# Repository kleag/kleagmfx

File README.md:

# Kleag's MFX

ADS1115
MCP23017
https://github.com/adafruit/Adafruit-MCP23017-Arduino-Library#pin-addressing

KY-040
n°4 on MCP@0x20
    - sw pin B1 (9)
    - but on A0, B0 (0, 8)

Pisound
Raspberry Pi 5 (4 should be OK)

Joystick: ADS.P0, ADS.P1
sudo apt install python3-uinput
sudo nano /etc/modules
uinput

Expression Pedal: ADS.P2

sudo nano /etc/udev/rules.d/99-uinput.rules
KERNEL=="uinput", SUBSYSTEM=="misc", MODE="0660", GROUP="input"
sudo usermod -a -G input $USER

`/boot/firmware/config.txt`:
```
display_auto_detect=1
dtparam=i2c_arm=on
dtparam=spi=on
dtparam=i2c_arm_baudrate=400000
dtoverlay=
dtoverlay=pisound
dtoverlay=vc4-kms-v3d
usb_max_current_enable=1
```

sudo raspi-config
```

Then go to:
`Interface Options → I2C → Enable → Reboot the Pi.`

```bash
sudo apt install -y i2c-tools
```

```bash
sudo i2cdetect -y 1
```

`/home/gael/.config/systemd/user/multieffect.service`
`/home/gael/.config/systemd/user/default.target.wants/multieffect.service -> /home/gael/.config/systemd/user/multieffect.service`

```ini
[Unit]
Description=Start Guitar Multi-Effect Python Script
After=graphical-session.target

[Service]
ExecStart=python /home/gael/multieffects/multieffect.py
WorkingDirectory=/home/gael
Restart=on-failure

[Install]
WantedBy=default.target
```

```bash
journalctl --user-unit multieffect.service
systemctl --user disable multieffect.service
systemctl --user enable multieffect.service
systemctl --user stop multieffect.service
systemctl --user start multieffect.service
```

# Disable wlan power management 
To avoid losing Wifi unexpectedly, disable its power management. Create `/etc/systemd/system/wifi-fix.service`:

```ini
[Unit]
Description=Disable WiFi Power Management
After=network.target

[Service]
Type=oneshot
ExecStart=/sbin/iwconfig wlan0 power off
RemainAfterExit=yes

[Install]
WantedBy=multi-user.target
```

and then enable the new service:
```bash
sudo systemctl enable wifi-fix.service
sudo systemctl start wifi-fix.service
```

# License

Copyright Gaël de Chalendar, 2025-2026.
This source describes Open Hardware and is licensed under the CERN-OHL-
W v2.
You may redistribute and modify this documentation and make products
using it under the terms of the CERN-OHL-W v2 (https:/cern.ch/cern-ohl).
This documentation is distributed WITHOUT ANY EXPRESS OR IMPLIED
WARRANTY, INCLUDING OF MERCHANTABILITY, SATISFACTORY QUALITY
AND FITNESS FOR A PARTICULAR PURPOSE. Please see the CERN-OHL-W v2
for applicable conditions.
Source location: https://github.com/kleag/kleagmfx
As per CERN-OHL-W v2 section 4.1, should You produce hardware based on
these sources, You must maintain the Source Location visible on the
external case of the Kleag's MFX or other product you make using
this documentation.

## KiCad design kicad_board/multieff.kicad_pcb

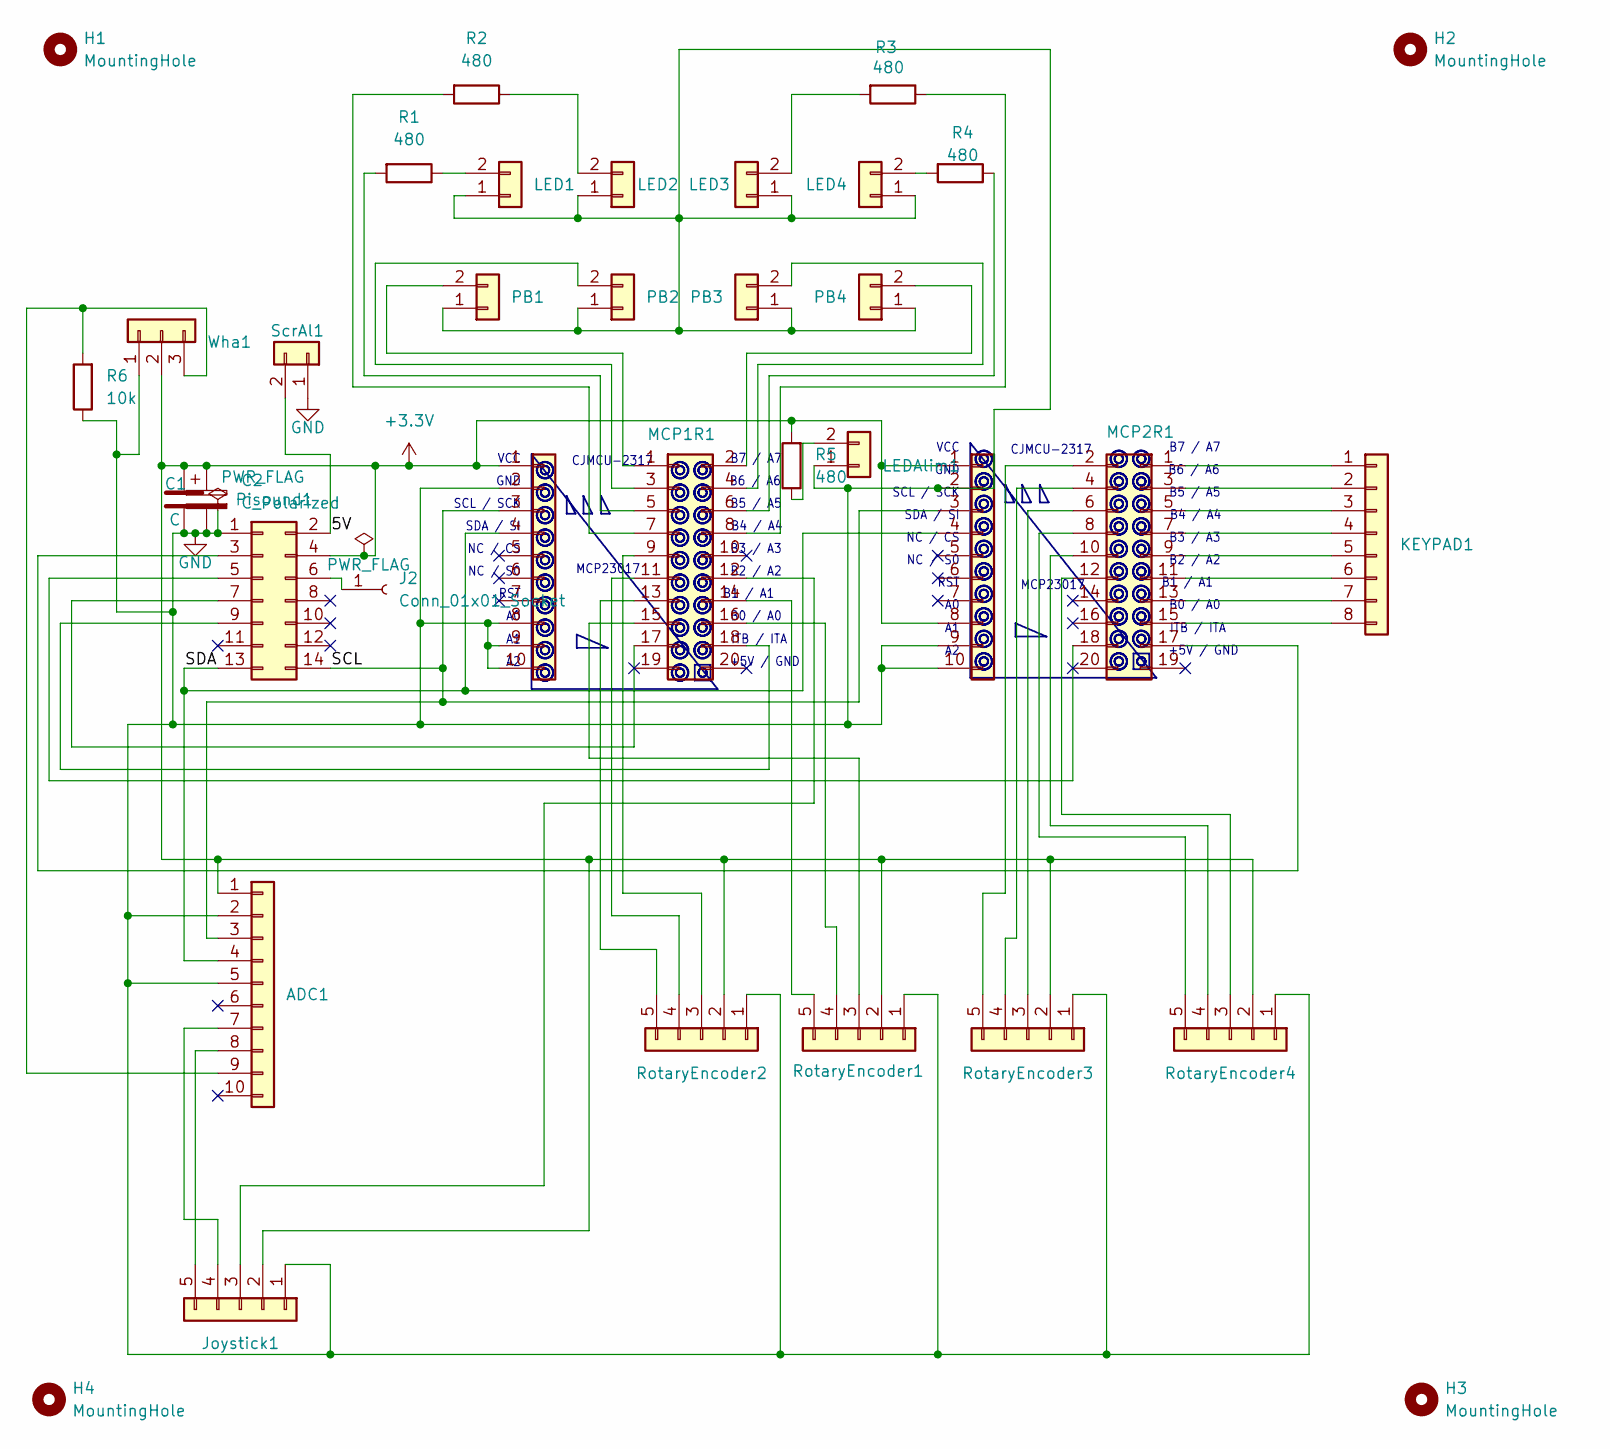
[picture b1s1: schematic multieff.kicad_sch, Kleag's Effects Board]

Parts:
ADC1: Conn_01x10; PinSocket_1x10_P2.54mm_Vertical
C1: C; C_Disc_D5.0mm_W2.5mm_P2.50mm
C2: C_Polarized; CP_Radial_D5.0mm_P2.00mm
H1, H2, H3, H4: MountingHole; MountingHole_3.2mm_M3
J2: Conn_01x01_Socket; PinSocket_1x01_P2.54mm_Vertical
Joystick1: Conn_01x05; JST_XH_B5B-XH-AM_1x05_P2.50mm_Vertical
KEYPAD1: Conn_01x08; PinSocket_1x08_P2.54mm_Vertical
LED1, LED2, LED3, LED4: Conn_01x02; JST_XH_B2B-XH-AM_1x02_P2.50mm_Vertical
LEDAlim1: Conn_01x02; JST_XH_B2B-XH-AM_1x02_P2.50mm_Vertical
MCD1L1: Conn_01x10; PinSocket_1x10_P2.54mm_Vertical
MCP1R1, MCP2R1: Conn_02x10_Odd_Even; PinSocket_2x10_P2.54mm_Vertical
MCP2L1: Conn_01x10; PinSocket_1x10_P2.54mm_Vertical
PB1, PB2, PB3, PB4: Conn_01x02; JST_XH_B2B-XH-AM_1x02_P2.50mm_Vertical
Pisound1: Conn_02x07_Odd_Even; PinSocket_2x07_P2.54mm_Vertical
R1, R2, R3, R4, R5: 480; R_Axial_DIN0309_L9.0mm_D3.2mm_P12.70mm_Horizontal
R6: 10k; R_Axial_DIN0309_L9.0mm_D3.2mm_P12.70mm_Horizontal
RotaryEncoder1, RotaryEncoder2, RotaryEncoder3, RotaryEncoder4: Conn_01x05; JST_XH_B5B-XH-AM_1x05_P2.50mm_Vertical
ScrAl1: Conn_01x02; JST_XH_B2B-XH-AM_1x02_P2.50mm_Vertical
WhaJack1: Wha1; JST_XH_B3B-XH-AM_1x03_P2.50mm_Vertical

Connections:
+3.3V: ADC1.1, C1.1, C2.1, Joystick1.2, MCD1L1.1, MCP2L1.1, MCP2L1.8, Pisound1.4, R5.2, RotaryEncoder1.2, RotaryEncoder2.2, RotaryEncoder3.2, RotaryEncoder4.2, WhaJack1.2
/5V: Pisound1.2, ScrAl1.2
/SCL: ADC1.3, MCD1L1.3, MCP2L1.3, Pisound1.14
/SDA: ADC1.4, MCD1L1.4, MCP2L1.4, Pisound1.13
GND: ADC1.2, ADC1.5, C1.2, C2.2, Joystick1.1, LED1.1, LED2.1, LED3.1, LED4.1, LEDAlim1.1, MCD1L1.2, MCD1L1.8, MCD1L1.9, MCD1L1.10, MCP2L1.2, MCP2L1.9, MCP2L1.10, PB1.1, PB2.1, PB3.1, PB4.1, Pisound1.1, R6.1, RotaryEncoder1.1, RotaryEncoder2.1, RotaryEncoder3.1, RotaryEncoder4.1, ScrAl1.1, WhaJack1.1
unnamed: ADC1.7, Joystick1.4
unnamed: ADC1.8, Joystick1.5
unnamed: ADC1.9, R6.2, WhaJack1.3
unnamed: J2.1, Pisound1.6
unnamed: Joystick1.3, MCP1R1.12
unnamed: KEYPAD1.1, MCP2R1.1
unnamed: KEYPAD1.2, MCP2R1.3
unnamed: KEYPAD1.3, MCP2R1.5
unnamed: KEYPAD1.4, MCP2R1.7
unnamed: KEYPAD1.5, MCP2R1.9
unnamed: KEYPAD1.6, MCP2R1.11
unnamed: KEYPAD1.7, MCP2R1.13
unnamed: KEYPAD1.8, MCP2R1.15
unnamed: LED1.2, R1.1
unnamed: LED2.2, R2.1
unnamed: LED3.2, R3.2
unnamed: LED4.2, R4.2
unnamed: LEDAlim1.2, R5.1
unnamed: MCP1R1.1, PB1.2
unnamed: MCP1R1.2, PB4.2
unnamed: MCP1R1.3, PB2.2
unnamed: MCP1R1.4, PB3.2
unnamed: MCP1R1.5, R1.2
unnamed: MCP1R1.6, R4.1
unnamed: MCP1R1.7, R2.2
unnamed: MCP1R1.8, R3.1
unnamed: MCP1R1.9, RotaryEncoder2.3
unnamed: MCP1R1.11, RotaryEncoder2.4
unnamed: MCP1R1.13, RotaryEncoder2.5
unnamed: MCP1R1.14, RotaryEncoder1.5
unnamed: MCP1R1.15, RotaryEncoder1.3
unnamed: MCP1R1.16, RotaryEncoder1.4
unnamed: MCP1R1.17, Pisound1.7
unnamed: MCP1R1.18, Pisound1.9
unnamed: MCP2R1.2, RotaryEncoder3.5
unnamed: MCP2R1.4, RotaryEncoder3.4
unnamed: MCP2R1.6, RotaryEncoder3.3
unnamed: MCP2R1.8, RotaryEncoder4.5
unnamed: MCP2R1.10, RotaryEncoder4.4
unnamed: MCP2R1.12, RotaryEncoder4.3
unnamed: MCP2R1.17, Pisound1.3
unnamed: MCP2R1.18, Pisound1.5

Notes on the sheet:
CJMCU-2317
MCP23017
B4 / A4
SDA / SI
SCL / SCK
GND
NC / CS
B5 / A5
VCC
NC / S0
B0 / A0
+5V / GND
B3 / A3
B1 / A1
B2 / A2
RST
B6 / A6
ITB / ITA
B7 / A7

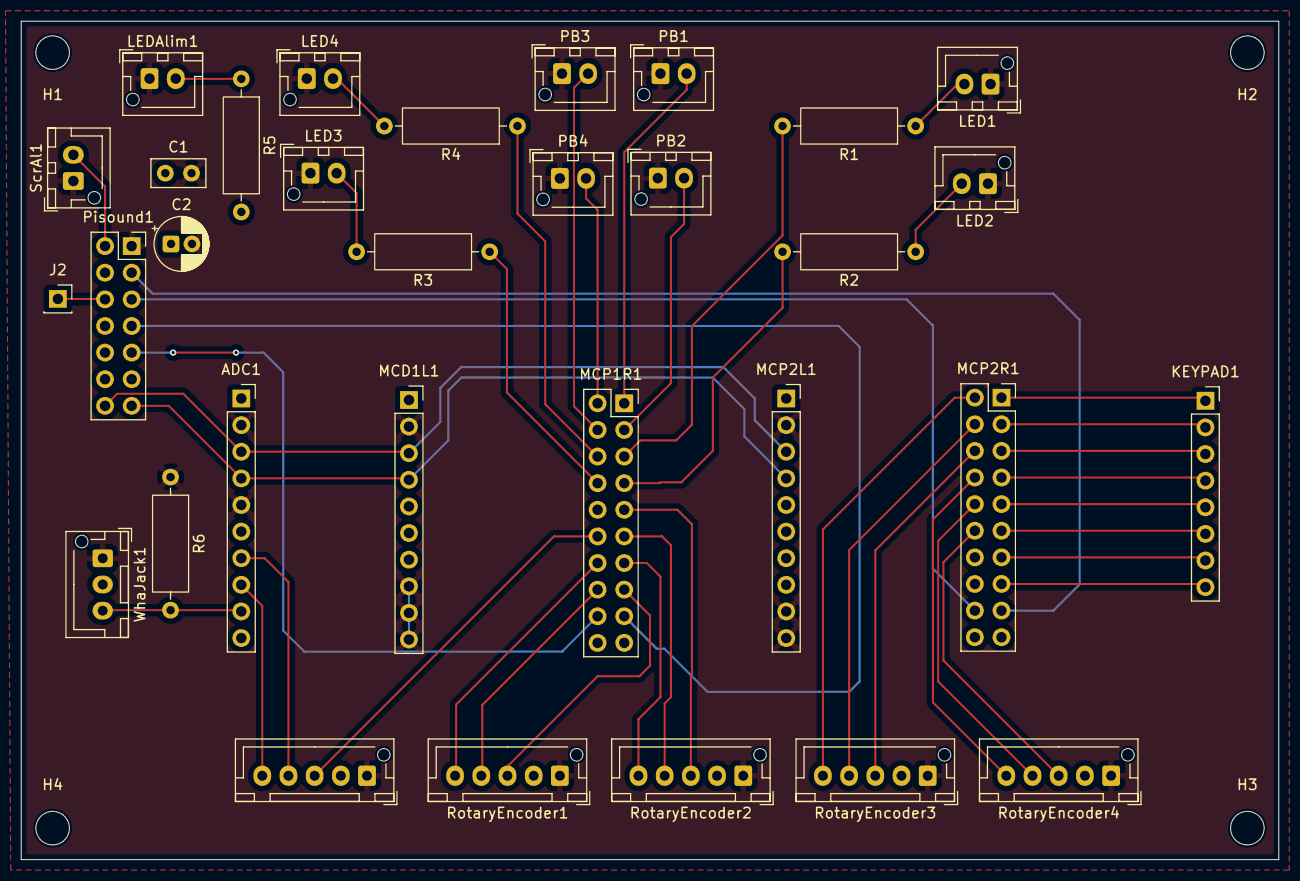
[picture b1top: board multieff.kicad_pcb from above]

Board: 2 copper layers, 120.0 x 80.0 mm, 36 parts (0 on the bottom side), 47 nets.

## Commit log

2025-10-10 Ignore generated files
2025-10-14 Working state
2025-10-14 Add information about the system service
2025-10-14 Add setup instructions
2025-10-16 Add a lot of information
2025-10-16 Add test scripts
2025-10-16 Ignore kdevelo files
2025-10-16 Latest pcb version
2025-10-16 Revert "Add a lot of information"
    This reverts commit c087858aa320d8767ea0a0a28b6813841709728a.
2025-10-16 Add lost data
2025-10-17 Add button to joystick test
2025-10-17 Add tests for keypads and leds
2025-10-17 Ignore Theia IDE files
2025-10-18 Correct keypad test code
2025-10-18 Correct pin numbers
2025-10-19 Give up with interrupts
2025-10-19 Joystick as mouse integrated
2025-10-19 First alpha of V2
2025-12-12 Joystick move works
2025-12-12 Clicking the joystick switch for midi learn works
2025-12-14 Rotary encoders switch added to buttons
2025-12-14 Refactoring to OOP
2025-12-14 Ignore python cache
2025-12-14 Use the correct mcp for joystick
2025-12-14 Add classes for KeyPad and Rotary encoders
2025-12-14 Communicate between threads with a queue
2025-12-14 A few details
2025-12-21 * and # keypad keys are L and R mouse buttons
2025-12-21 Can type presets number above 9
2025-12-29 Correct mouse buttons clicking implementation
2026-01-25 Synchronize physics and soft
2026-02-15 Add connector for expression pedal
2026-02-15 Add component numbering
2026-02-15 Add gitignore
2026-02-15 With zones and jst connectors
2026-02-15 Sent to production
2026-03-02 Correct traces geometry
2026-03-02 Improve connectors placement
2026-03-03 First mcp23017 chip schema
2026-03-04 Ongoing work
2026-03-04 Work in progress
2026-03-04 Correct joystick jst orientation
2026-03-05 Add License
2026-03-05 First complete IC based version
    Still miss some decoupling condensators.
2026-03-06 Chips decoupling complete
2026-03-06 Add decoupling capacitors to LEDs
2026-03-22 Aprroaching fabrication
2026-03-22 Add missing screen alim connector
2026-03-22 Update rotary encoder tests
2026-03-22 Add handling of expression pedal
2026-04-05 Rotary encoders work
2026-04-05 Add support for expression pedal
    Needed to add lock on joystick i2c read to avoid conflicts.
2026-04-05 Remove debug messages
2026-04-05 Rotary encoders interruption based work
2026-04-05 Work on interruption based rotary encoders
2026-04-06 Improved expression pedal handling
2026-04-06 Add notes to the board
2026-04-23 Correct expression pedal settings
2026-04-23 Start to make a proper project
2026-04-23 Instructionf for wifi connection
2026-04-23 Improve joystick response
2026-04-23 Bump tqdm from 4.64.1 to 4.66.3
    Bumps [tqdm](https://github.com/tqdm/tqdm) from 4.64.1 to 4.66.3.
    - [Release notes](https://github.com/tqdm/tqdm/releases)
    - [Commits](https://github.com/tqdm/tqdm/compare/v4.64.1...v4.66.3)
    ---
    updated-dependencies:
    - dependency-name: tqdm
2026-04-23 Add documentation
2026-04-23 Add CI for docs
2026-04-23 Test
2026-04-23 Test 2 for docs
2026-04-23 Start the real doc
2026-04-23 Deployed 1b0b75d with MkDocs version: 1.6.1
